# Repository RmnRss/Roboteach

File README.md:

# Roboteach
## Qu’est-ce que Roboteach ?
 
Roboteach est un outil pédagogique, permettant aux élèves de cycle 2 (écoles primaires) et de cycle 3 (collèges) d’appréhender les grands principes de la robotique et de l’informatique. 

Il permet aux élèves de construire des petits robots et de les programmer pour faire ce qu’ils souhaitent.

Ce projet utilise du matériel Fischertechnik qui est piloté depuis un ordinateur sous Windows 7 ou plus récent, grâce au logiciel mBlock 3 et a une interface physique branchée sur une carte Arduino Uno. 

## Prendre en main Roboteach :
 
### Les prérequis.
* **Une boite Roboteach** (contenant une prise d’alimentation, une carte Arduino Uno et une interface de pilotage).
* **Du matériel Fischertechnik** : Blocs de constructions, éléments électronique, bornier, moteur à courant continu etc.
* Un ordinateur sous **Windows 7 ou plus récent.**
* Le logiciel **mBlock 3.0** à télécharger ici.
* L’extension mBlock **Roboteach.zip** à télécharger ici.

### Installation et Configuration.
#### Installation de mBlock 3.
On va tout d’abord commencer par installer mBlock 3 sur votre machine.

Si ça n’est pas déjà fait téléchargez mBlock 3 ici.

Lancez le fichier téléchargé et suivez les instructions d’installation du logiciel.

Une fois installé, lancez le logiciel pour vérifier qu’il fonctionne correctement.

Vous pouvez changer la langue du logiciel en allant dans le **Menu Langage > Français**.

Si vous ne possédez pas les pilotes Arduino, installez-les en cliquant sur le menu **Connecter > Installer les pilotes Arduino**. Attendez que l’installation se termine.

#### Installation de l’extension Roboteach sur mBlock 3
Si ça n’est pas déjà fait téléchargez l’extension ici.

Ouvrez mBlock.

Cliquez ensuite sur Choix des Extensions > Gérer les extensions.

Dans la nouvelle petite fenêtre, cliquez en bas à droite sur le bouton **Ajouter**.

Sélectionnez le fichier **Roboteach.zip** préalablement téléchargé.

L’extension devrait maintenant apparaitre dans la section **Installées** de la fenêtre **Gérer les extensions**.

Fermez la fenêtre **Gérer les extensions** et cliquez ensuite sur la section **Pilotage** des blocs dans laquelle vous devriez maintenant voir apparaitre les blocs Roboteach.

Si ça n’est pas le cas vérifier que Roboteach est bien coché dans le menu **Choix Des Extensions**.

### Configuration du Matériel
#### Branchements du matériel
1. Branchez la boîte Roboteach en USB sur votre ordinateur (prise blanche sur la boite).
2. Branchez les deux extrémités Rouge et Verte de l’adaptateur secteur aux extrémités rouge et verte de la boite Roboteach, en respectant bien les couleurs, le rouge sur le rouge et le vert sur le vert.
3. Branchez ensuite votre bornier à la boite Roboteach, en respectant bien le sens indiqué par le détrompeur de la boite.
4. Enfin, branchez ensuite adaptateur secteur sur le secteur.

### Paramétrage de la carte avec mBlock
#### Une fois la carte branchée en USB et mBlock lancé.
Cliquez sur le menu **Choix de la carte > Arduino Uno**. Assurez-vous ensuite que Arduino Uno est bien coché dans le menu.

Cliquez sur le menu **Connecter > par Port Série COM > Le port sur lequel est branché l’Arduino** (COM9 par exemple). Si vous n’avez que l’Arduino de branché sur l’ordinateur il ne devrait vous être présenté qu’un choix.

Une fois le port sélectionné cliquez une nouvelle fois sur le menu **Connecter > Téléverser le microprogramme de communication**. Attendez que le programme se téléverse.

Si tout s’est bien passé vous devriez voir apparaitre un rond vert à coté de **Roboteach** dans la section **Pilotage**. Vous êtes donc prêt à utiliser les blocs.

## Test de fonctionnement
 
Pour s’assurer que tout fonctionne correctement, nous allons essayer de faire démarrer un moteur. 
#### Matériel :
Branchez un moteur sur une des bornes M du bornier Fischertechnik, la borne M2 par exemple.
#### Logiciel :
Placez ensuite un bloc « **Démarrer le moteur M2 dans le sens POSITIF** ». Si vous avez branché votre moteur sur les bornes M2, sinon choisissez en conséquence.
Cliquez sur ce bloc, si le moteur démarre alors tout est bien branché. Vous pouvez l’arrêter en cliquant sur le bloc « Arrêt d’Urgence », ou bien en utilisant le bloc « **Arrêter le moteur M2** ».

## Détail des blocs

* Arrêt d’urgence

Permet d’arrêter toutes les actions en cours et de réinitialiser toutes les valeurs de la carte à 0.

---
* Démarrer le moteur **M1/M2/M3/M4** dans le sens **POSITIF/NEGATIF**.

Démarre le moteur branché sur la sortie M sélectionnée, dans le sens choisis.

---
* Arrêter le moteur **M1/M2/M3/M4**.

Stop le moteur branché sur la sortie M sélectionnée.

---
* Allumer la lampe **M1/M2/M3/M4**.

Allume la lampe branchée sur la sortie M sectionnée.

---
* Éteindre la lampe **M1/M2/M3/M4**.

Éteint la lampe branchée sur la sortie M sectionnée.

---
* Activer l’aimant **M1/M2/M3/M4**.

Active l’aimant branchée sur la sortie M sectionnée.

---
* Désactiver l’aimant **M1/M2/M3/M4**.

Désactive l’aimant branchée sur la sortie M sectionnée.

---
* Actualiser l’entrée **E1/E2/E3/E4/E5/E6/E7/E8**.

Permet au registre à décalage d’envoyer la bonne entrée vers le pin lu par l’Arduino.

---
* Valeur de **E1/E2/E3/E4/E5/E6/E7/E8**.

Donne la valeur digitale (binaire) de l’entrée sélectionnée.

```diff
- ATTENTION : Ce bloc doit toujours être précédé du bloc « Actualiser l’entrée E ». Et les entrées des deux blocs doivent être identiques. Donc si on souhaite lire la valeur de l’entrée E5, je dois sélectionner E5 sur les deux blocs.
```

---

* Booléen de **E1/E2/E3/E4/E5/E6/E7/E8**.`

Donne la valeur de l’entrée sélectionnée sous forme booléenne (vrai ou faux).

```diff
- ATTENTION : Ce bloc doit toujours être précédé du bloc « Actualiser l’entrée E ». Et les entrées des deux blocs doivent être identiques. Donc si on souhaite lire la valeur de l’entrée E5, je dois sélectionner E5 sur les deux blocs.
```

---
* Valeur de **EX/EY**.

Donne la valeur analogique du matériel branché sur l’entrée sélectionnée.

## Outils utilisés

*	Autodesk EAGLE – Pour les typons de l’interface.
*	Notepad++ – Pour l’écriture de l’extension mBlock.

## Auteurs

*	Rousseau Romain – Stagiaire à l’ENSIM – Conception de l’interface, et code de l’extension.
*	Pascal Leroux – Professeur des Universités à l’ENSIM - Créateur de Roboteach en 1998 et encadrant du projet.

## Remerciements

*	Au personnel de l’ENSIM, pour leur aide tout au long du projet.
*	Merci à Daniel Puglièse, Jean-Pierre Remoué, Marc Tavera et Christophe Aubier pour leurs conseils avisés.

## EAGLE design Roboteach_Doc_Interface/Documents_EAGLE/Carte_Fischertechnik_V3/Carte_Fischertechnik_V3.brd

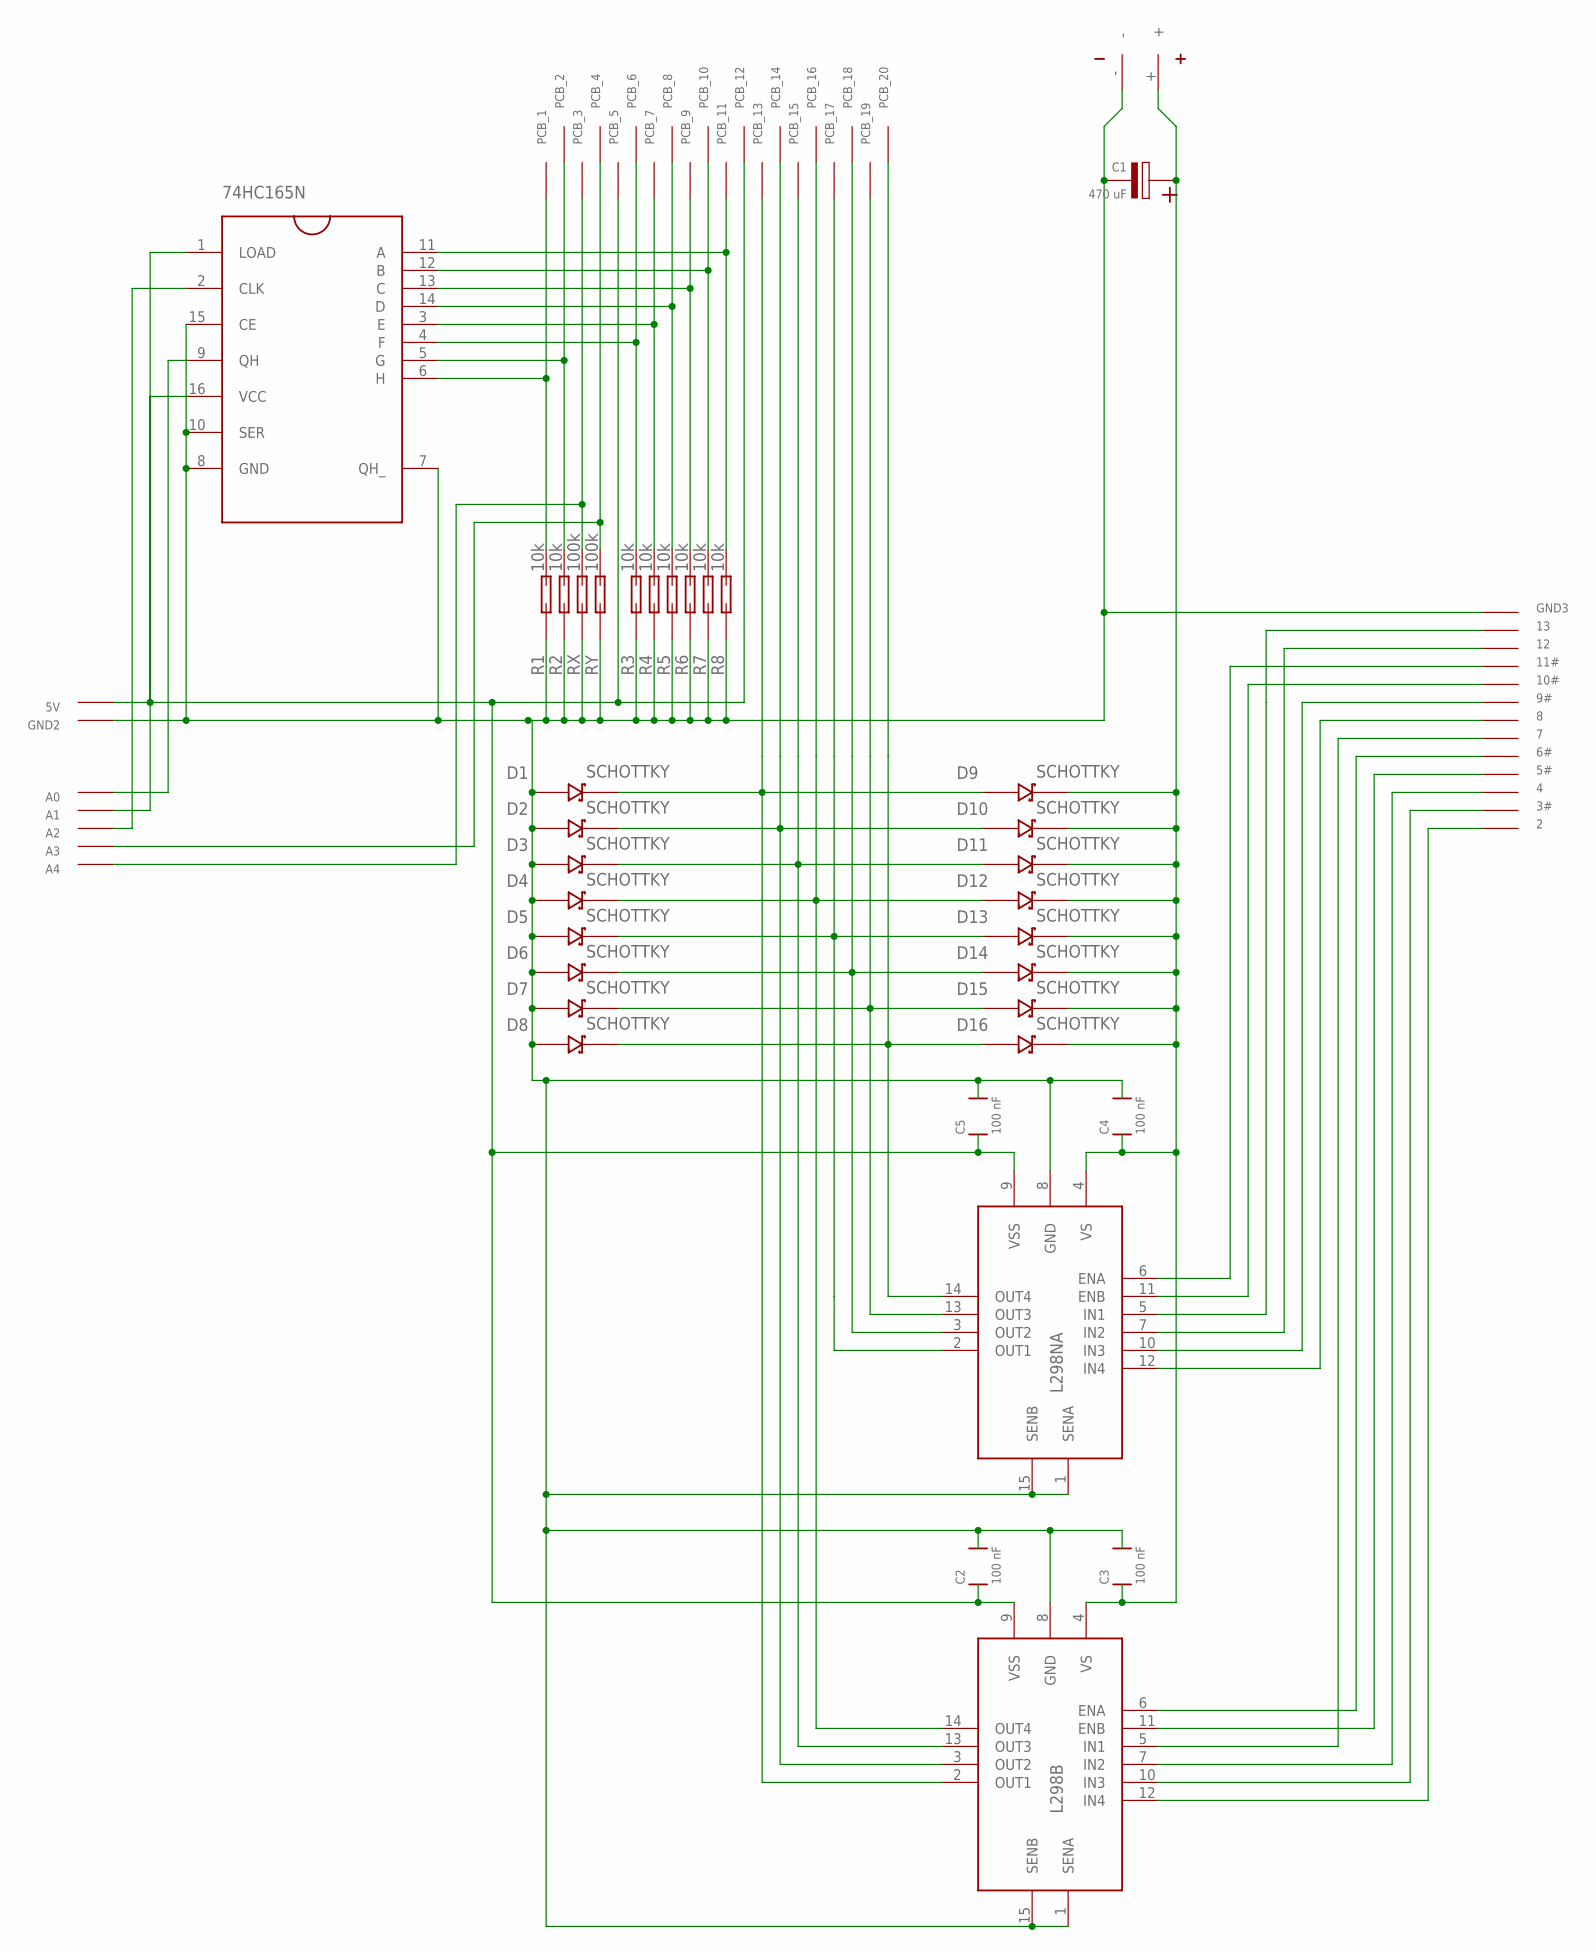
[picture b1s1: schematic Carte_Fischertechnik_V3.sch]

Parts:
2, 3#, 4, 5#, 6#, 7, 8, 9#, 10#, 11#, 12, 13: PAD_O
5V: 5V; PAD_O
74HC165N: 74HC165N
A0, A1, A2, A3, A4: PAD_O
C1: 470 uF; POLARIZED_CAPACITOR
C2, C3, C4, C5: 100 nF; CAPACITOR
D1, D2, D3, D4, D5, D6, D7, D8, D9, D10, D11, D12, D13, D14, D15, D16: SCHOTTKY
GND2: GND; PAD_O
GND3: PAD_O
L298B, L298NA: L298N
PCB_1, PCB_2, PCB_3, PCB_4, PCB_5, PCB_6, PCB_7, PCB_8, PCB_9, PCB_10, PCB_11, PCB_12, PCB_13, PCB_14, PCB_15, PCB_16, PCB_17, PCB_18, PCB_19, PCB_20: PAD_C
R1, R2, R3, R4, R5, R6, R7, R8: 10k; RESISTANCE
RX: 100k; RESISTANCE
RY: 100k; RESISTANCE
U$1: ADAPTATEUR_FTK

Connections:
unnamed: D1.+, D9.-, L298B.2 (OUT1), PCB_13.$1
unnamed: 5V.P$1, 74HC165N.16 (VCC), C2.P$1, C5.P$1, L298B.9 (VSS), L298NA.9 (VSS), PCB_5.$1, PCB_12.$1
unnamed: 74HC165N.5 (G), PCB_2.$1, R2.P$2 (B)
unnamed: D2.+, D10.-, L298B.3 (OUT2), PCB_14.$1
unnamed: D3.+, D11.-, L298B.13 (OUT3), PCB_15.$1
unnamed: 74HC165N.7 (QH_), 74HC165N.8 (GND), 74HC165N.10 (SER), 74HC165N.15 (CE), C1.P$2 (-), C2.P$2, C3.P$2, C4.P$2, C5.P$2, D1.-, D2.-, D3.-, D4.-, D5.-, D6.-, D7.-, D8.-, GND2.P$1, GND3.P$1, L298B.1 (SENA), L298B.8 (GND), L298B.15 (SENB), L298NA.1 (SENA), L298NA.8 (GND), L298NA.15 (SENB), R1.P$1 (A), R2.P$1 (A), R3.P$1 (A), R4.P$1 (A), R5.P$1 (A), R6.P$1 (A), R7.P$1 (A), R8.P$1 (A), RX.P$1 (A), RY.P$1 (A), U$1.-
unnamed: D5.+, D13.-, L298NA.2 (OUT1), PCB_17.$1
unnamed: C1.P$1 (+), C3.P$1, C4.P$1, D9.+, D10.+, D11.+, D12.+, D13.+, D14.+, D15.+, D16.+, L298B.4 (VS), L298NA.4 (VS), U$1.+
unnamed: D4.+, D12.-, L298B.14 (OUT4), PCB_16.$1
unnamed: 74HC165N.9 (QH), A0.P$1
unnamed: 74HC165N.2 (CLK), A2.P$1
unnamed: 74HC165N.1 (LOAD), A1.P$1
unnamed: 74HC165N.6 (H), PCB_1.$1, R1.P$2 (B)
unnamed: A4.P$1, PCB_3.$1, RX.P$2 (B)
unnamed: A3.P$1, PCB_4.$1, RY.P$2 (B)
unnamed: 74HC165N.4 (F), PCB_6.$1, R3.P$2 (B)
unnamed: 74HC165N.3 (E), PCB_7.$1, R4.P$2 (B)
unnamed: 74HC165N.14 (D), PCB_8.$1, R5.P$2 (B)
unnamed: 74HC165N.13 (C), PCB_9.$1, R6.P$2 (B)
unnamed: 74HC165N.12 (B), PCB_10.$1, R7.P$2 (B)
unnamed: 74HC165N.11 (A), PCB_11.$1, R8.P$2 (B)
unnamed: 11#.P$1, L298NA.6 (ENA)
unnamed: 10#.P$1, L298NA.11 (ENB)
unnamed: 13.P$1, L298NA.5 (IN1)
unnamed: 12.P$1, L298NA.7 (IN2)
unnamed: D6.+, D14.-, L298NA.3 (OUT2), PCB_18.$1
unnamed: D7.+, D15.-, L298NA.13 (OUT3), PCB_19.$1
unnamed: D8.+, D16.-, L298NA.14 (OUT4), PCB_20.$1
unnamed: 9#.P$1, L298NA.10 (IN3)
unnamed: 8.P$1, L298NA.12 (IN4)
unnamed: 7.P$1, L298B.5 (IN1)
unnamed: 6#.P$1, L298B.6 (ENA)
unnamed: 5#.P$1, L298B.11 (ENB)
unnamed: 4.P$1, L298B.7 (IN2)
unnamed: 3#.P$1, L298B.10 (IN3)
unnamed: 2.P$1, L298B.12 (IN4)

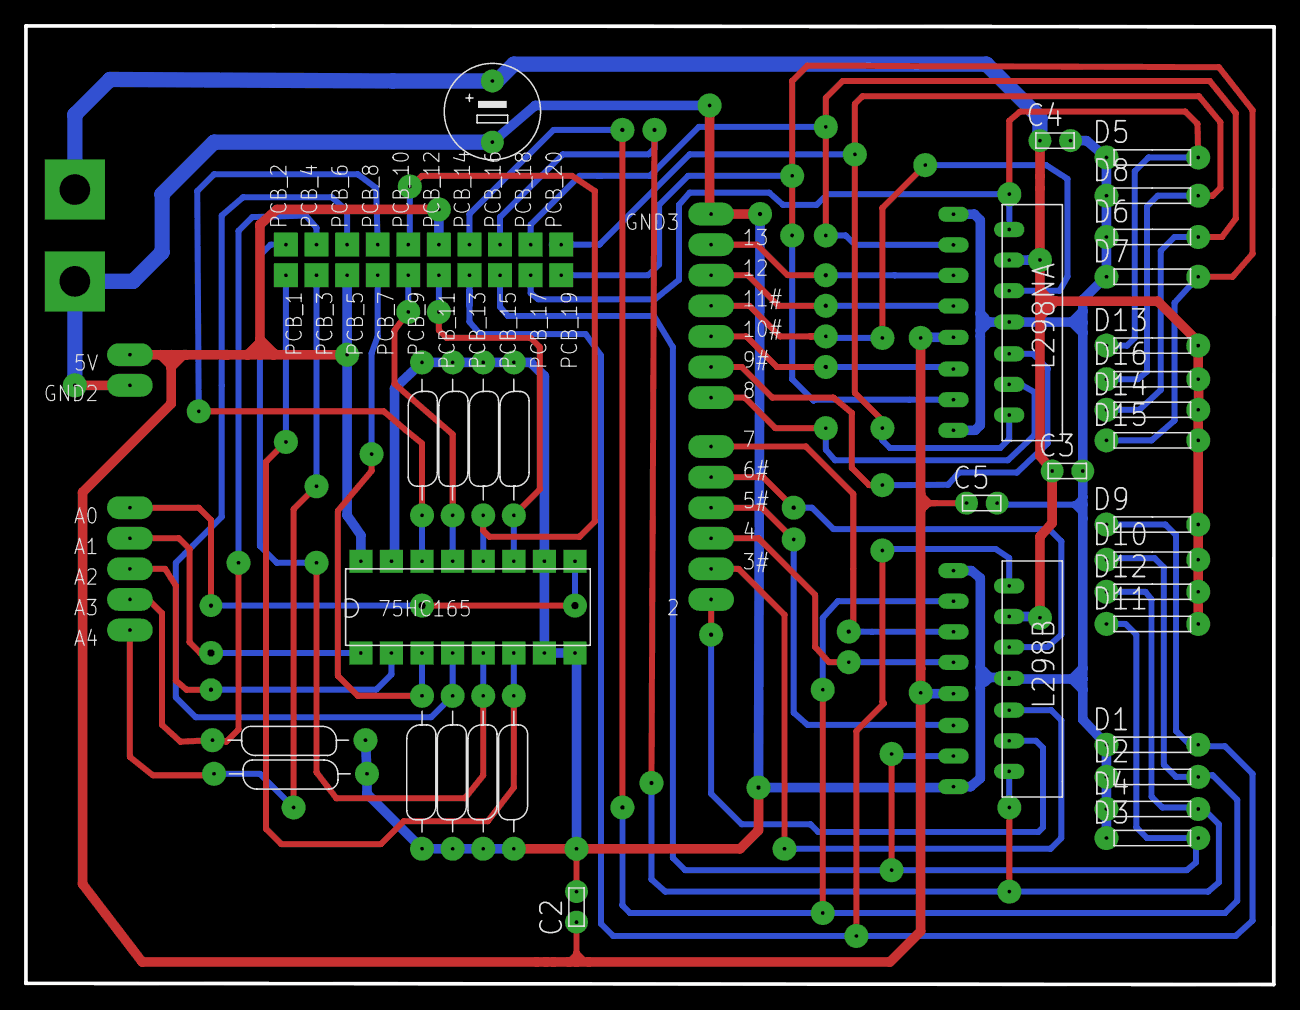
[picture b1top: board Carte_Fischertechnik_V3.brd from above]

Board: 2 copper layers, 103.6 x 79.6 mm, 75 parts (0 on the bottom side), 36 nets.

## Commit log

2018-02-27 First Push
2018-03-02 Dernière version
    02/03/2018
2018-06-01 Fichiers mBlock - Bug e-binaires 1bloc
    Fonctionnel sauf binaires qui demande 2 appuis
2018-06-15 Cleaning
2018-06-28 Python Fonctionnel
    Ajout de la classe Fischertechnik permettant de piloter les éléments depuis Python 3.6 grâce à la bibliotèque PyMata_AIO
2018-06-28 Nettoyage et Ajout
    Ajout des Documents - Datasheets, Pin Map, Projet EAGLE etc.
2018-07-04 add readme
2018-07-04 Adding ReadMe
2018-07-05 wording
